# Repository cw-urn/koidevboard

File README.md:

# koidevboard

> What is this?
- koiboard, but the RP2040 development board version.
> How do you use it?
- Everybody knows how to use a devboard...
> Why did I make this?
- Boredom, and I thought it would be interesting and I'd learn from it. I did!

## 3D render

## PCB

### Layer 1

### Layer 2

### Schematic

## JLCPCB cart

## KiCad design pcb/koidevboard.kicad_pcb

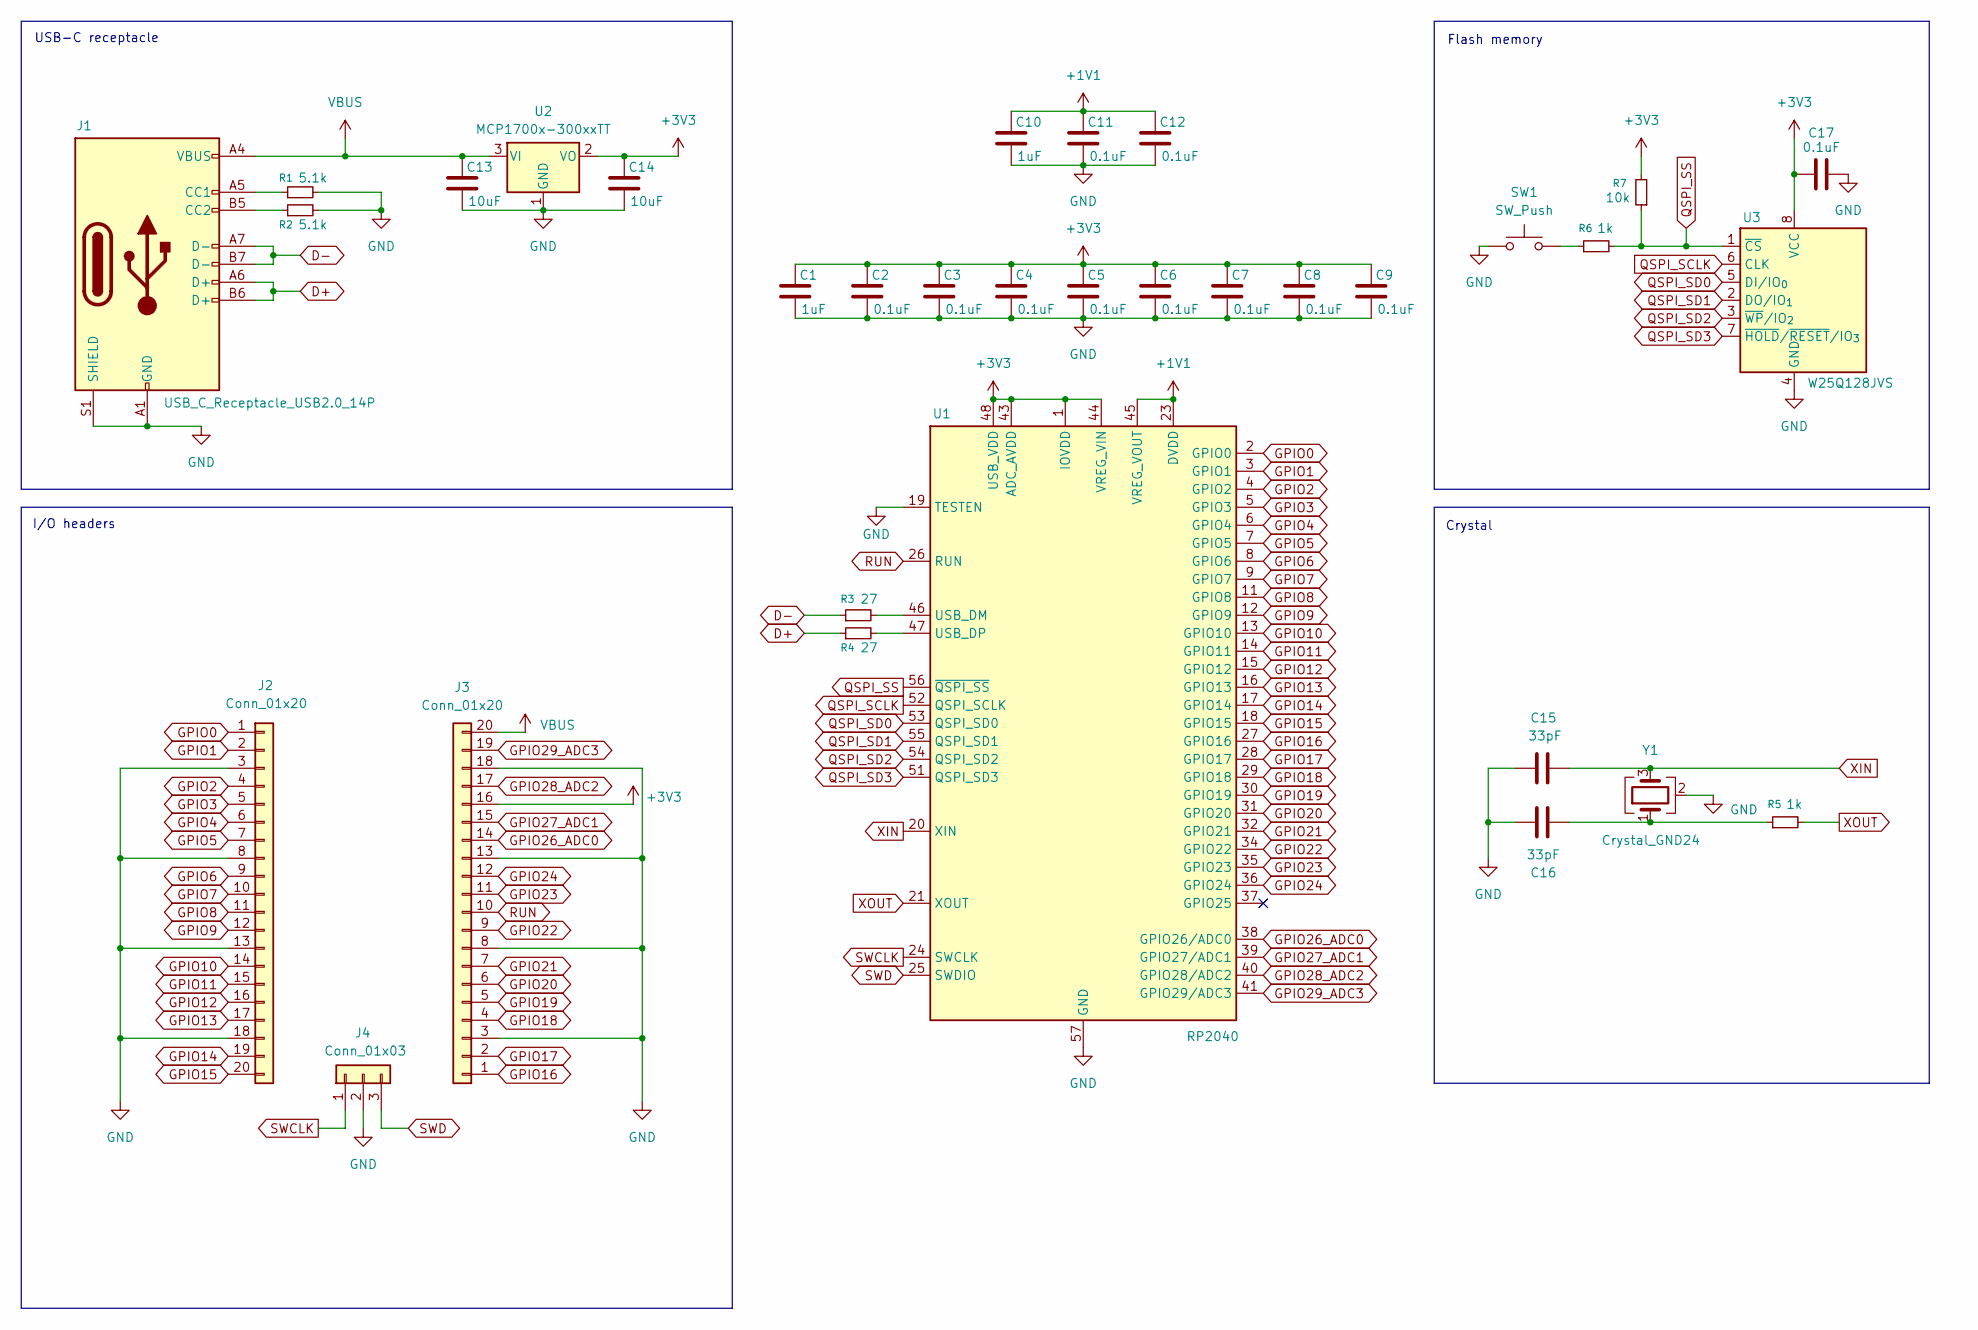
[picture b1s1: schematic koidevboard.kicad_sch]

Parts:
C1, C10: 1uF; C_0402_1005Metric
C2, C3, C4, C5, C6, C7, C8, C9, C11, C12, C17: 0.1uF; C_0402_1005Metric
C13, C14: 10uF; C_0603_1608Metric
C15, C16: 33pF; C_0402_1005Metric
J1: USB_C_Receptacle_USB2.0_14P; USB_C_Receptacle_HRO_TYPE-C-31-M-12
J2, J3: Conn_01x20; PinHeader_1x20_P2.54mm_Vertical
J4: Conn_01x03; PinHeader_1x03_P2.54mm_Vertical
R1, R2: 5.1k; C_0402_1005Metric
R3, R4: 27; C_0402_1005Metric
R5, R6: 1k; C_0402_1005Metric
R7: 10k; C_0402_1005Metric
SW1: SW_Push; SW_Push_SPST_NO_Alps_SKRK
U1: RP2040; QFN-56-1EP_7x7mm_P0.4mm_EP3.2x3.2mm
U2: MCP1700x-300xxTT; SOT-23
U3: W25Q128JVS; Winbond_USON-8-1EP_3x2mm_P0.5mm_EP0.2x1.6mm
Y1: Crystal_GND24; Crystal_SMD_3225-4Pin_3.2x2.5mm

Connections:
+1V1: C10.1, C11.1, C12.1, U1.23 (DVDD), U1.45 (VREG_VOUT), U1.50 (DVDD)
+3V3: C1.1, C2.1, C3.1, C4.1, C5.1, C6.1, C7.1, C8.1, C9.1, C14.1, C17.1, J3.16, R7.2, U1.1 (IOVDD), U1.10 (IOVDD), U1.22 (IOVDD), U1.33 (IOVDD), U1.42 (IOVDD), U1.43 (ADC_AVDD), U1.44 (VREG_VIN), U1.48 (USB_VDD), U1.49 (IOVDD), U2.2 (VO), U3.8 (VCC)
D+: J1.A6 (D+), J1.B6 (D+), R4.1
D-: J1.A7 (D-), J1.B7 (D-), R3.1
GND: C1.2, C2.2, C3.2, C4.2, C5.2, C6.2, C7.2, C8.2, C9.2, C10.2, C11.2, C12.2, C13.2, C14.2, C15.2, C16.2, C17.2, J1.A1 (GND), J1.A12 (GND), J1.B1 (GND), J1.B12 (GND), J1.S1 (SHIELD), J2.3, J2.8, J2.13, J2.18, J3.3, J3.8, J3.13, J3.18, J4.2, R1.2, R2.2, SW1.1, U1.19 (TESTEN), U1.57 (GND), U2.1 (GND), U3.4 (GND), Y1.2 (G), Y1.4 (G); also elsewhere on the board
GPIO0: J2.1, U1.2 (GPIO0)
GPIO1: J2.2, U1.3 (GPIO1)
GPIO2: J2.4, U1.4 (GPIO2)
GPIO3: J2.5, U1.5 (GPIO3)
GPIO4: J2.6, U1.6 (GPIO4)
GPIO5: J2.7, U1.7 (GPIO5)
GPIO6: J2.9, U1.8 (GPIO6)
GPIO7: J2.10, U1.9 (GPIO7)
GPIO8: J2.11, U1.11 (GPIO8)
GPIO9: J2.12, U1.12 (GPIO9)
GPIO10: J2.14, U1.13 (GPIO10)
GPIO11: J2.15, U1.14 (GPIO11)
GPIO12: J2.16, U1.15 (GPIO12)
GPIO13: J2.17, U1.16 (GPIO13)
GPIO14: J2.19, U1.17 (GPIO14)
GPIO15: J2.20, U1.18 (GPIO15)
GPIO16: J3.1, U1.27 (GPIO16)
GPIO17: J3.2, U1.28 (GPIO17)
GPIO18: J3.4, U1.29 (GPIO18)
GPIO19: J3.5, U1.30 (GPIO19)
GPIO20: J3.6, U1.31 (GPIO20)
GPIO21: J3.7, U1.32 (GPIO21)
GPIO22: J3.9, U1.34 (GPIO22)
GPIO23: J3.11, U1.35 (GPIO23)
GPIO24: J3.12, U1.36 (GPIO24)
GPIO26_ADC0: J3.14, U1.38 (GPIO26/ADC0)
GPIO27_ADC1: J3.15, U1.39 (GPIO27/ADC1)
GPIO28_ADC2: J3.17, U1.40 (GPIO28/ADC2)
GPIO29_ADC3: J3.19, U1.41 (GPIO29/ADC3)
unnamed: C16.1, R5.1, Y1.1
unnamed: J1.A5 (CC1), R1.1
unnamed: J1.B5 (CC2), R2.1
unnamed 37: R6.1, SW1.2; also elsewhere on the board
unnamed: R3.2, U1.46 (USB_DM)
unnamed: R4.2, U1.47 (USB_DP)
QSPI_SCLK: U1.52 (QSPI_SCLK), U3.6 (CLK)
QSPI_SD0: U1.53 (QSPI_SD0), U3.5 (DI/IO_{0})
QSPI_SD1: U1.55 (QSPI_SD1), U3.2 (DO/IO_{1})
QSPI_SD2: U1.54 (QSPI_SD2), U3.3 (~WP/IO_{2})
QSPI_SD3: U1.51 (QSPI_SD3), U3.7 (~HOLD/~RESET/IO_{3})
QSPI_SS: R6.2, R7.1, U1.56 (~QSPI_SS), U3.1 (~CS)
RUN: J3.10, U1.26 (RUN)
SWCLK: J4.1, U1.24 (SWCLK)
SWD: J4.3, U1.25 (SWDIO)
VBUS: C13.1, J1.A4 (VBUS), J1.A9 (VBUS), J1.B4 (VBUS), J1.B9 (VBUS), J3.20, U2.3 (VI)
XIN: C15.1, U1.20 (XIN), Y1.3
XOUT: R5.2, U1.21 (XOUT)

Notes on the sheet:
Flash memory
USB-C receptacle
I/O headers
Crystal

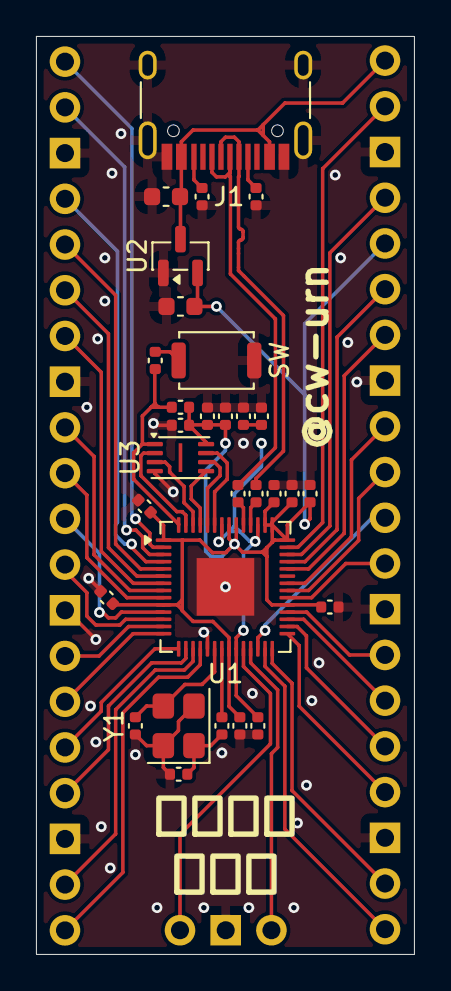
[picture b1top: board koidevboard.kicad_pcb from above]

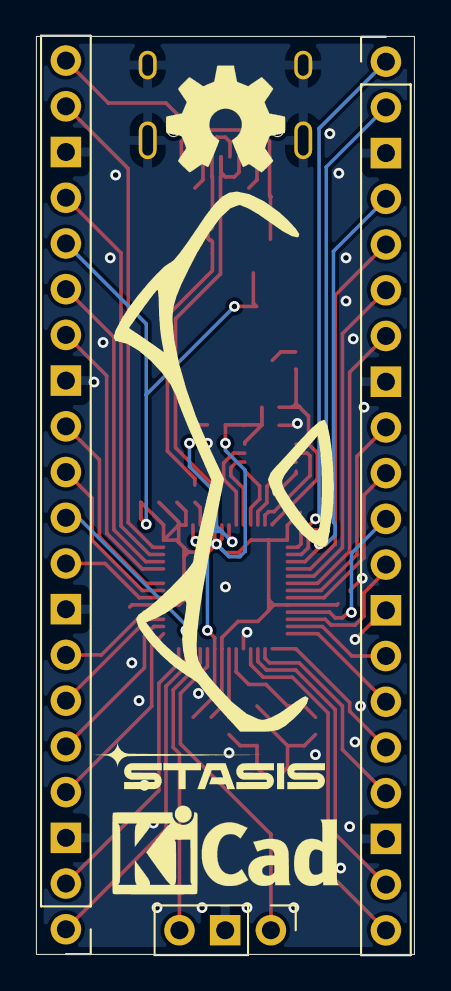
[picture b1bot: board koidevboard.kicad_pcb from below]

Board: 2 copper layers, 21.0 x 51.0 mm, 33 parts (3 on the bottom side), 52 nets.

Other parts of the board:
SW: SW_Push; SW_Push_SPST_NO_Alps_SKRK

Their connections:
GND: SW.1; also elsewhere on the board
unnamed 37: SW.2; also elsewhere on the board

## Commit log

2026-04-03 schemantic
2026-04-06 silkscreen
2026-04-08 square pads
2026-04-08 images
2026-04-08 ultra readme
2026-04-08 ultra readme 2
2026-04-22 WM8960
